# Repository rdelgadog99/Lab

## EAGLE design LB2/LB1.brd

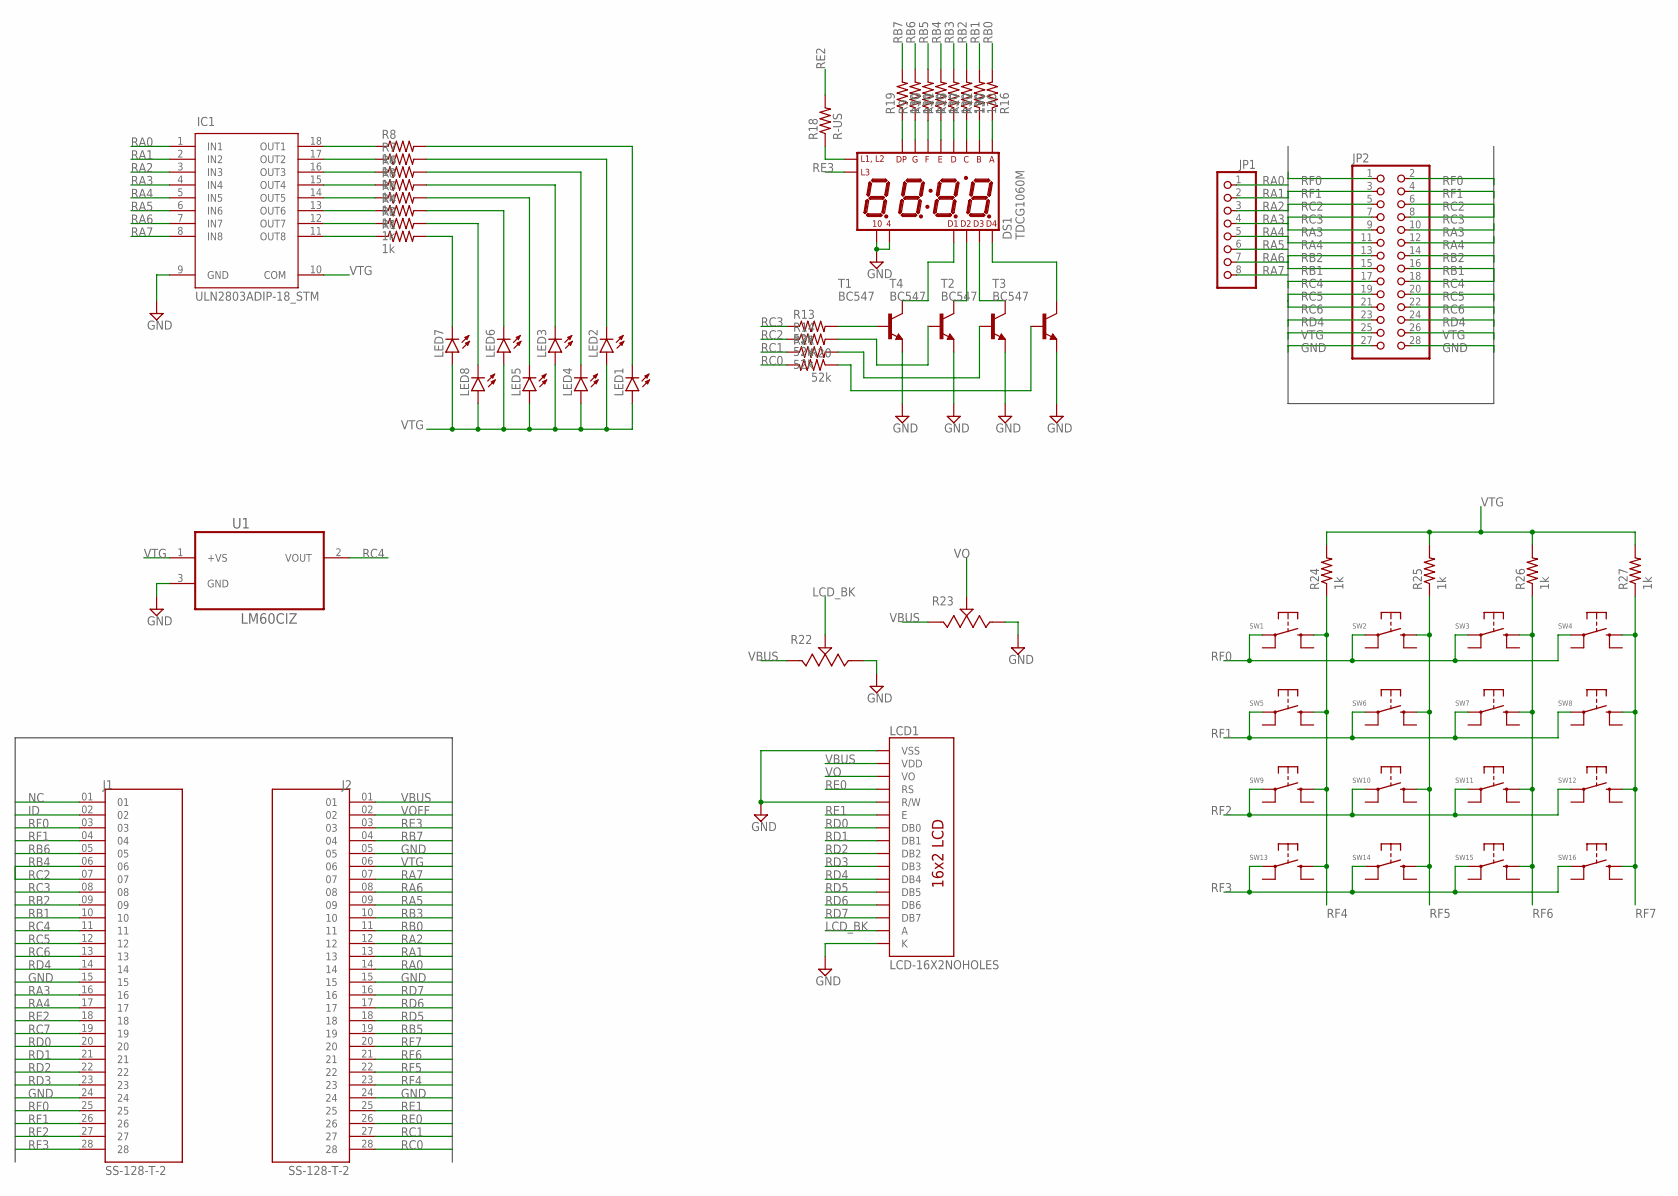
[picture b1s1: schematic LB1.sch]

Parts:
DS1: TDCG1060M; DISPLAY_TDCG1060M
IC1: ULN2803ADIP-18_STM; DIP-18_STM
J1, J2: SS-128-T-2; SAMTEC_SS-128-T-2
JP1: PINHD-1X8BIG; 1X08-BIG
JP2: PINHD-2X14-CB; 2X14-BIG
LCD1: LCD-16X2NOHOLES; LCD-16X2_NOHOLESNOSILK
LED1, LED2, LED3, LED4, LED5, LED6, LED7, LED8: LED3MM
R1, R2, R3, R4, R5, R6, R7, R8, R24, R25, R26, R27: 1k; 0207/10
R9, R10, R11, R12, R15, R16, R17, R19: 130; 0207/10
R13, R14, R20, R21: 52k; 0207/10
R18: R-US; 0207/10
R22, R23: 3362P-1-103LF
SW1, SW2, SW3, SW4, SW5, SW6, SW7, SW8, SW9, SW10, SW11, SW12, SW13, SW14, SW15, SW16: 1825910-2; TE_1825910-2
T1, T2, T3, T4: BC547; TO92
U1: LM60CIZ; TO92/

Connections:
GND: DS1.4, DS1.10, IC1.9 (GND), J1.15, J1.24, J2.05, J2.15, J2.24, JP2.27, JP2.28, LCD1.1 (VSS), LCD1.5 (R/W), LCD1.16 (K), R22.3, R23.3, T1.1 (E), T2.1 (E), T3.1 (E), T4.1 (E), U1.3 (GND)
ID: J1.02
LCD_BK: LCD1.15 (A), R22.2
unnamed: IC1.11 (OUT8), R1.1
unnamed: IC1.15 (OUT4), R3.1
unnamed: IC1.18 (OUT1), R8.1
unnamed: IC1.17 (OUT2), R7.1
unnamed: IC1.16 (OUT3), R6.1
unnamed: IC1.14 (OUT5), R5.1
unnamed: IC1.13 (OUT6), R4.1
unnamed: IC1.12 (OUT7), R2.1
unnamed: LED7.K (C), R1.2
unnamed: LED8.K (C), R2.2
unnamed: LED6.K (C), R4.2
unnamed: LED5.K (C), R5.2
unnamed: LED3.K (C), R3.2
unnamed: LED4.K (C), R6.2
unnamed: LED2.K (C), R7.2
unnamed: LED1.K (C), R8.2
unnamed: DS1.15 (G), R9.1
unnamed: DS1.7 (DP), R19.1
unnamed: DS1.5 (E), R11.1
unnamed: DS1.3 (D), R15.1
unnamed: DS1.13 (C), R17.1
unnamed: DS1.16 (B), R12.1
unnamed: DS1.14 (A), R16.1
unnamed: DS1.12 (L1_L2), R18.1
unnamed: R13.2, T1.2 (B)
unnamed: R14.2, T4.2 (B)
unnamed: R21.2, T2.2 (B)
unnamed: DS1.1 (DIG1), T1.3 (C)
unnamed: R20.1, T3.2 (B)
unnamed: DS1.2 (DIG2), T4.3 (C)
unnamed: DS1.6 (DIG3), T2.3 (C)
unnamed: DS1.8 (DIG4), T3.3 (C)
NC: J1.01
RA0: IC1.1 (IN1), J2.14, JP1.1
RA1: IC1.2 (IN2), J2.13, JP1.2
RA2: IC1.3 (IN3), J2.12, JP1.3
RA3: IC1.4 (IN4), J1.16, JP1.4, JP2.9, JP2.10
RA4: IC1.5 (IN5), J1.17, JP1.5, JP2.11, JP2.12
RA5: IC1.6 (IN6), J2.09, JP1.6
RA6: IC1.7 (IN7), J2.08, JP1.7
RA7: IC1.8 (IN8), J2.07, JP1.8
RB0: J2.11, R16.2
RB1: J1.10, JP2.15, JP2.16, R12.2
RB2: J1.09, JP2.13, JP2.14, R17.2
RB3: J2.10, R15.2
RB4: J1.06, R11.2
RB5: J2.19, R10.2
RB6: DS1.11 (F), J1.05, R9.2, R10.1
RB7: J2.04, R19.2
RC0: J2.28, R20.2
RC1: J2.27, R21.1
RC2: J1.07, JP2.5, JP2.6, R14.1
RC3: J1.08, JP2.7, JP2.8, R13.1
RC4: J1.11, JP2.17, JP2.18, U1.2 (VOUT)
RC5: J1.12, JP2.19, JP2.20
RC6: J1.13, JP2.21, JP2.22
RC7: J1.19
RD0: J1.20, LCD1.7 (DB0)
RD1: J1.21, LCD1.8 (DB1)
RD2: J1.22, LCD1.9 (DB2)
RD3: J1.23, LCD1.10 (DB3)
RD4: J1.14, JP2.23, JP2.24, LCD1.11 (DB4)
RD5: J2.18, LCD1.12 (DB5)
RD6: J2.17, LCD1.13 (DB6)
RD7: J2.16, LCD1.14 (DB7)
RE0: J2.26, LCD1.4 (RS)
RE1: J2.25, LCD1.6 (E)
RE2: J1.18, R18.2
RE3: DS1.9 (L3), J2.03
RF0: J1.03, J1.25, JP2.1, JP2.2, SW1.1, SW2.1, SW3.1, SW4.1
RF1: J1.04, J1.26, JP2.3, JP2.4, SW5.1, SW6.1, SW7.1, SW8.1
RF2: J1.27, SW9.1, SW10.1, SW11.1, SW12.1
RF3: J1.28, SW13.1, SW14.1, SW15.1, SW16.1
RF4: J2.23, R24.1, SW1.2 (S), SW5.2 (S), SW9.2 (S), SW13.2 (S)
RF5: J2.22, R25.1, SW2.2 (S), SW6.2 (S), SW10.2 (S), SW14.2 (S)
RF6: J2.21, R26.1, SW3.2 (S), SW7.2 (S), SW11.2 (S), SW15.2 (S)
RF7: J2.20, R27.1, SW4.2 (S), SW8.2 (S), SW12.2 (S), SW16.2 (S)
VBUS: J2.01, LCD1.2 (VDD), R22.1, R23.1
VO: LCD1.3 (VO), R23.2
VOFF: J2.02
VTG: IC1.10 (COM), J2.06, JP2.25, JP2.26, LED1.A, LED2.A, LED3.A, LED4.A, LED5.A, LED6.A, LED7.A, LED8.A, R24.2, R25.2, R26.2, R27.2, U1.1 (+VS)

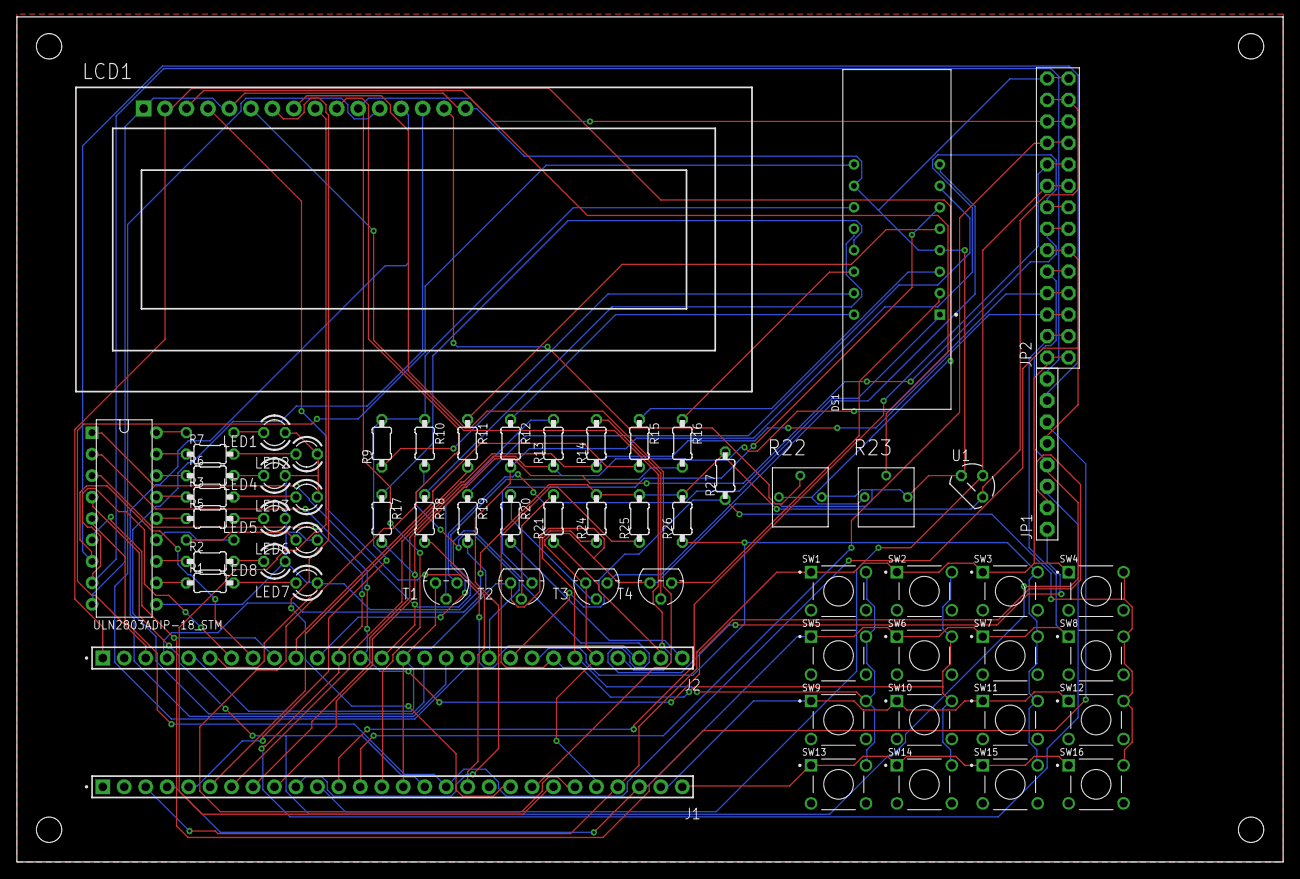
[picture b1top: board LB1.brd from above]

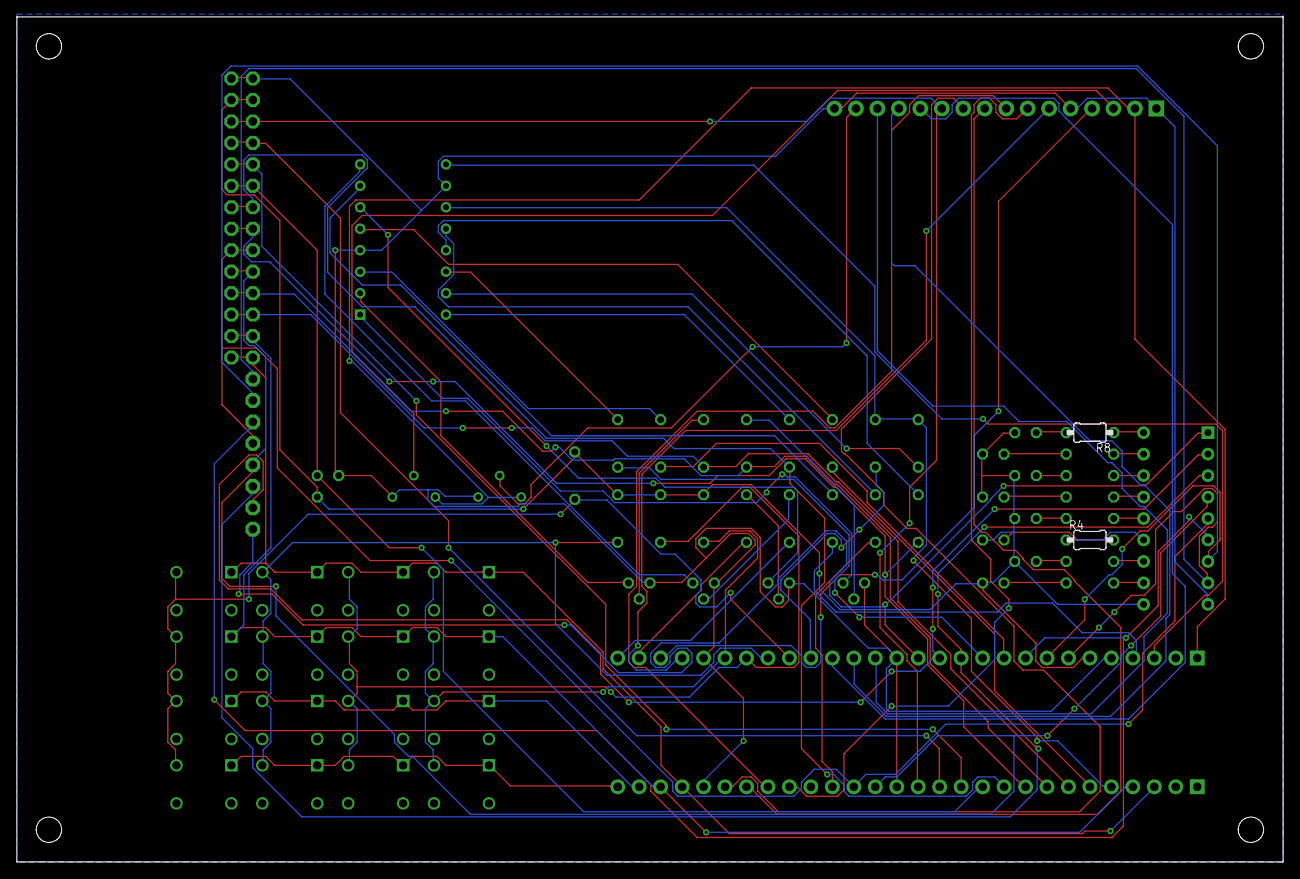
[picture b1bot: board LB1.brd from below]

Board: 2 copper layers, 149.8 x 100.0 mm, 63 parts (2 on the bottom side), 80 nets.

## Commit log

2022-09-05 Create LB3
2022-09-20 Create LB4

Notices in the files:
parts and their libraries:
COPYRIGHT: Copyright (C) 2022 Ultra Librarian. All rights reserved.
